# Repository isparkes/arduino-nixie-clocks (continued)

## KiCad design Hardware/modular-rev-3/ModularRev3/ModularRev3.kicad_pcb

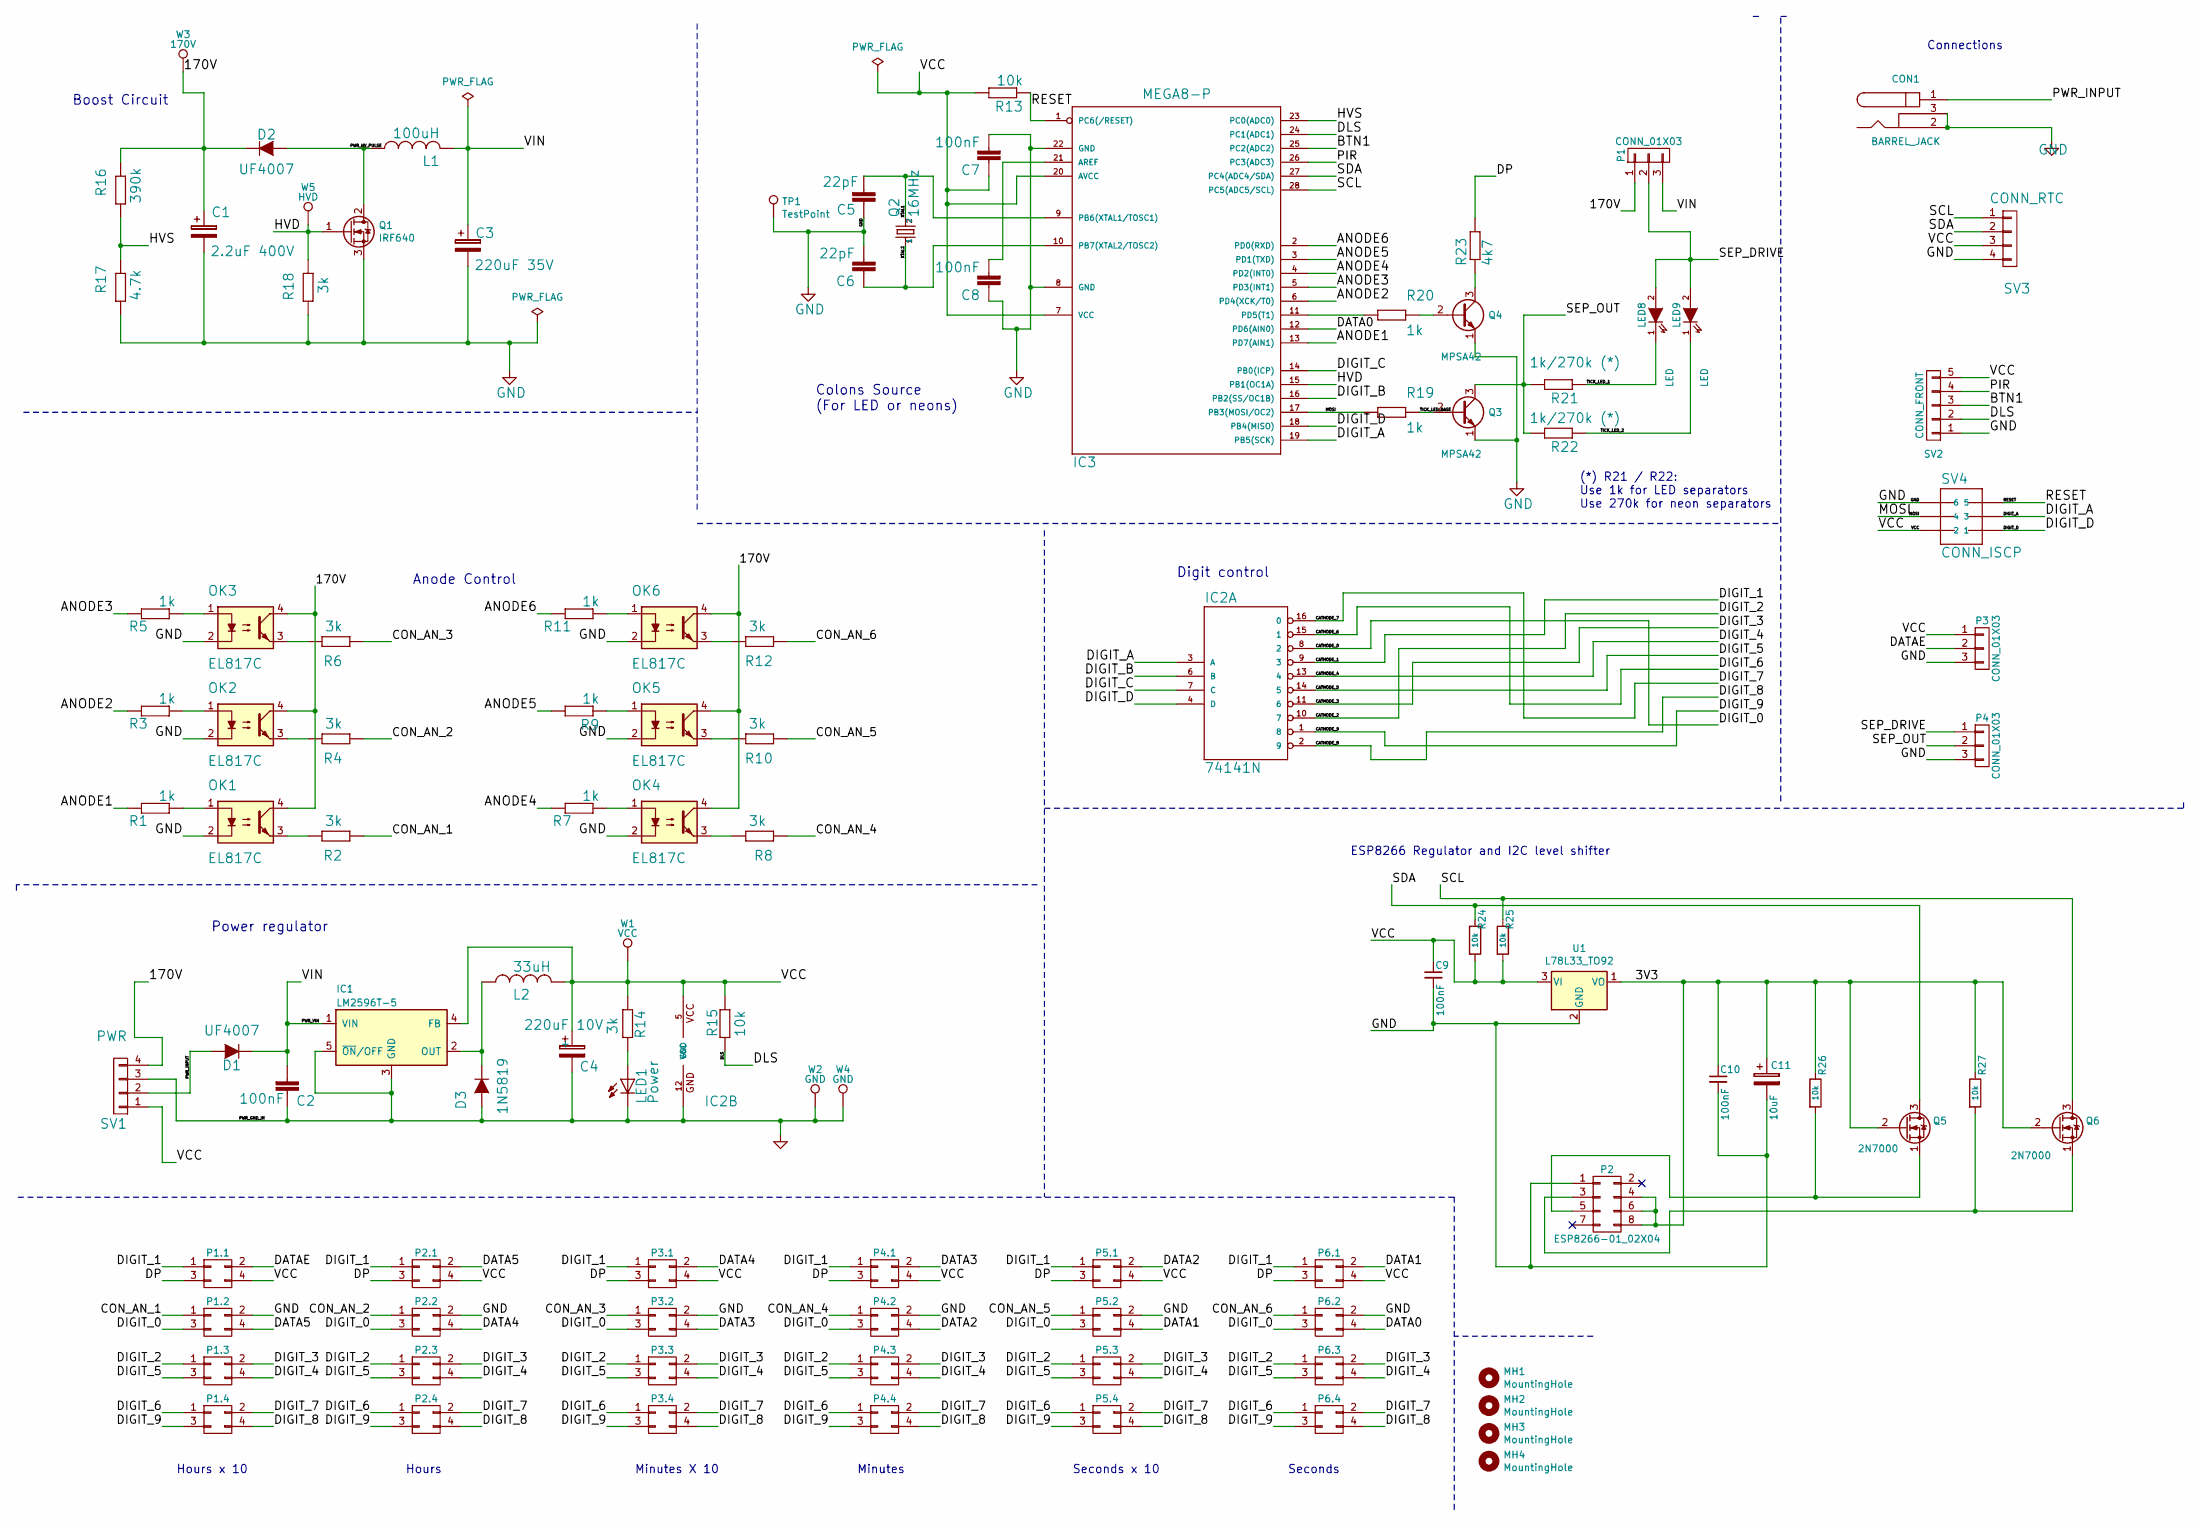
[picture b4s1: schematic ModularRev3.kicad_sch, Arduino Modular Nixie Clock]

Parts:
C1: 2.2uF 400V; C_Radial_D8_L11.5_P3.5
C2, C7, C8, C9, C10: 100nF; C025-024X044
C3: 220uF 35V; C_Radial_D8_L11.5_P3.5
C4: 220uF 10V; C_Radial_D6.3_L11.2_P2.5
C5, C6: 22pF; C025-024X044
C11: 10uF; C_Radial_D6.3_L11.2_P2.5
CON1: BARREL_JACK
D1, D2: UF4007; Diode_DO-41_SOD81_Vertical_AnodeUp
D3: 1N5819; Diode_DO-41_SOD81_Vertical_AnodeUp
IC1: LM2596T-5; TO220-5A_H
IC2: 74141N; 74141_DIL16
IC3: MEGA8-P; 328P_DIL28
L1: 100uH; Inductor-100mH
L2: 33uH; Inductor-33mH-TH-SMD
LED1: Power; LED_3MM
LED8, LED9: LED; LED-5MM-Centred
MH1, MH2, MH3, MH4: MountingHole; MountingHole_3.2mm_M3
OK1, OK2, OK3, OK4, OK5, OK6: EL817C; optocoupler-DIL04
P1: CONN_01X03; SOLDER-JUMPER_2-WAY
P1.1, P1.2, P1.3, P1.4, P2.1, P2.2, P2.3, P2.4, P3.1, P3.2, P3.3, P3.4, P4.1, P4.2, P4.3, P4.4, P5.1, P5.2, P5.3, P5.4, P6.1, P6.2, P6.3, P6.4: CONN_02X02; Header_MA02-2
P2: ESP8266-01_02X04; ESP8266_2x04
P3, P4: CONN_01X03; Header_MA03-1
Q1: IRF640; TO-220-3_H
Q2: 16MHz; Crystal_HC49-U_Vertical
Q3, Q4: MPSA42; TO-92_inline_MPSA42
Q5, Q6: 2N7000; TO-92_2N7000_inline
R1, R3, R5, R7, R9, R11, R19, R20: 1k; R-0207_2V
R2, R4, R6, R8, R10, R12, R14, R18: 3k; R-0207_2V
R13, R15, R24, R25, R26, R27: 10k; R-0207_2V
R16: 390k; R-0207_2V
R17: 4.7k; R-0207_2V
R21, R22: 1k/270k (*); R-0207_2V
R23: 4k7; R-0207_2V
SV1: PWR; Header_MA04-1
SV2: CONN_FRONT; Header_MA05-1
SV3: CONN_RTC; Header_MA04-1
SV4: CONN_ISCP; Header_MA03-2
TP1: TestPoint; TestPoint_THTPad_1.0x1.0mm_Drill0.5mm
U1: L78L33_TO92; TO-92_Inline
W1: VCC; TESTPAD_P1-13
W2, W4: GND; TESTPAD_P1-13
W3: 170V; TESTPAD_P1-13
W5: HVD; TESTPAD_P1-13

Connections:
/3V3: C10.1, C11.1, P2.4 (CH_EN), P2.6 (RST), P2.8 (VCC), Q5.2 (G), Q6.2 (G), R26.1, R27.1, U1.1 (VO)
/170V: C1.1, D2.1 (K), OK1.4, OK2.4, OK3.4, OK4.4, OK5.4, OK6.4, P1.1, R16.2, SV1.4, W3.1
/ANODE1: IC3.13 (PD7(AIN1)), R1.2
/ANODE2: IC3.6 (PD4(XCK/T0)), R3.2
/ANODE3: IC3.5 (PD3(INT1)), R5.2
/ANODE4: IC3.4 (PD2(INT0)), R7.2
/ANODE5: IC3.3 (PD1(TXD)), R9.2
/ANODE6: IC3.2 (PD0(RXD)), R11.2
/BTN1: IC3.25 (PC2(ADC2)), SV2.3
/CATHODE_0: IC2.8 (2), P1.2.3, P2.2.3, P3.2.3, P4.2.3, P5.2.3, P6.2.3
/CATHODE_1: IC2.9 (3), P1.1.1, P2.1.1, P3.1.1, P4.1.1, P5.1.1, P6.1.1
/CATHODE_2: IC2.10 (7), P1.3.1, P2.3.1, P3.3.1, P4.3.1, P5.3.1, P6.3.1
/CATHODE_3: IC2.11 (6), P1.3.2, P2.3.2, P3.3.2, P4.3.2, P5.3.2, P6.3.2
/CATHODE_4: IC2.13 (4), P1.3.4, P2.3.4, P3.3.4, P4.3.4, P5.3.4, P6.3.4
/CATHODE_5: IC2.14 (5), P1.3.3, P2.3.3, P3.3.3, P4.3.3, P5.3.3, P6.3.3
/CATHODE_6: IC2.15 (1), P1.4.1, P2.4.1, P3.4.1, P4.4.1, P5.4.1, P6.4.1
/CATHODE_7: IC2.16 (0), P1.4.2, P2.4.2, P3.4.2, P4.4.2, P5.4.2, P6.4.2
/CATHODE_8: IC2.2 (9), P1.4.4, P2.4.4, P3.4.4, P4.4.4, P5.4.4, P6.4.4
/CATHODE_9: IC2.1 (8), P1.4.3, P2.4.3, P3.4.3, P4.4.3, P5.4.3, P6.4.3
/CON_AN_1: P1.2.1, R2.1
/CON_AN_2: P2.2.1, R4.1
/CON_AN_3: P3.2.1, R6.1
/CON_AN_4: P4.2.1, R8.1
/CON_AN_5: P5.2.1, R10.1
/CON_AN_6: P6.2.1, R12.1
/DATA0: IC3.12 (PD6(AIN0)), P6.2.4
/DATA1: P5.2.4, P6.1.2
/DATA2: P4.2.4, P5.1.2
/DATA3: P3.2.4, P4.1.2
/DATA4: P2.2.4, P3.1.2
/DATA5: P1.2.4, P2.1.2
/DATAE: P1.1.2, P3.2
/DIGIT_A: IC2.3 (A), IC3.19 (PB5(SCK)), SV4.3
/DIGIT_B: IC2.6 (B), IC3.16 (PB2(SS/OC1B))
/DIGIT_C: IC2.7 (C), IC3.14 (PB0(ICP))
/DIGIT_D: IC2.4 (D), IC3.18 (PB4(MISO)), SV4.1
/DLS: IC3.24 (PC1(ADC1)), R15.1, SV2.2
/DP: P1.1.3, P2.1.3, P3.1.3, P4.1.3, P5.1.3, P6.1.3, R23.2
/HVD: IC3.15 (PB1(OC1A)), Q1.1 (G), R18.2, W5.1
/HVS: IC3.23 (PC0(ADC0)), R16.1, R17.2
/MOSI: IC3.17 (PB3(MOSI/OC2)), R19.1, SV4.4
/PIR: IC3.26 (PC3(ADC3)), SV2.4
/PWR_HV_PULSE: D2.2 (A), L1.1, Q1.2 (D)
/PWR_INPUT: CON1.1, D1.2 (A), SV1.2
/PWR_VIN: C2.2, C3.1, D1.1 (K), IC1.1 (VIN), L1.2, P1.3
/RESET: IC3.1 (PC6(/RESET)), R13.1, SV4.5
/SCL: IC3.28 (PC5(ADC5/SCL)), Q6.3 (D), R25.1, SV3.1
/SDA: IC3.27 (PC4(ADC4/SDA)), Q5.3 (D), R24.1, SV3.2
/SEP_DRIVE: LED8.2 (A), LED9.2 (A), P1.2, P4.1
/SEP_OUT: P4.2, Q3.3 (C), R21.2, R22.2
/TICK_LED_1: LED8.1 (K), R21.1
/TICK_LED_2: LED9.1 (K), R22.1
/TICK_LED_BASE: Q3.2 (B), R19.2
/VCC: C4.1, C7.1, C9.1, IC1.4 (FB), IC2.5 (VCC), IC3.7 (VCC), IC3.20 (AVCC), L2.2, P1.1.4, P2.1.4, P3.1, P3.1.4, P4.1.4, P5.1.4, P6.1.4, R13.2, R14.1, R15.2, R24.2, R25.2, SV1.1, SV2.5, SV3.3, SV4.2, U1.3 (VI), W1.1
/XTAL1: C5.2, IC3.9 (PB6(XTAL1/TOSC1)), Q2.2
/XTAL2: C6.1, IC3.10 (PB7(XTAL2/TOSC2)), Q2.1
GND: C1.2, C2.1, C3.2, C4.2, C5.1, C6.2, C7.2, C8.1, C9.2, C10.2, C11.2, CON1.2, CON1.3, D3.2 (A), IC1.3 (GND), IC1.5 (~ON/OFF), IC2.12 (GND), IC3.8 (GND), IC3.22 (GND), LED1.K (C), OK1.2, OK2.2, OK3.2, OK4.2, OK5.2, OK6.2, P1.2.2, P2.1 (GND), P2.2.2, P3.3, P3.2.2, P4.3, P4.2.2, P5.2.2, P6.2.2, Q1.3 (S), Q3.1 (E), Q4.1 (E), R17.1, R18.1, SV1.3, SV2.1, SV3.4, SV4.6, TP1.1, U1.2 (GND), W2.1, W4.1
unnamed: C8.2, IC3.21 (AREF)
unnamed: D3.1 (K), IC1.2 (OUT), L2.1
unnamed: IC3.11 (PD5(T1)), R20.1
unnamed: LED1.A, R14.2
unnamed: OK1.1, R1.1
unnamed: OK1.3, R2.2
unnamed: OK2.1, R3.1
unnamed: OK2.3, R4.2
unnamed: OK3.1, R5.1
unnamed: OK3.3, R6.2
unnamed: OK4.1, R7.1
unnamed: OK4.3, R8.2
unnamed: OK5.1, R9.1
unnamed: OK5.3, R10.2
unnamed: OK6.1, R11.1
unnamed: OK6.3, R12.2
unnamed: P2.3 (GPIO2), Q6.1 (S), R27.2
unnamed: P2.5 (GPIO0), Q5.1 (S), R26.2
unnamed: Q4.2 (B), R20.2
unnamed: Q4.3 (C), R23.1

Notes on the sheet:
Seconds x 10
Minutes
Digit control
Seconds
ESP8266 Regulator and I2C level shifter
(*) R21 / R22: Use 1k for LED separators Use 270k for neon separators
Hours
Minutes X 10
Anode Control
Colons Source (For LED or neons)
Power regulator
Connections
Boost Circuit
Hours x 10

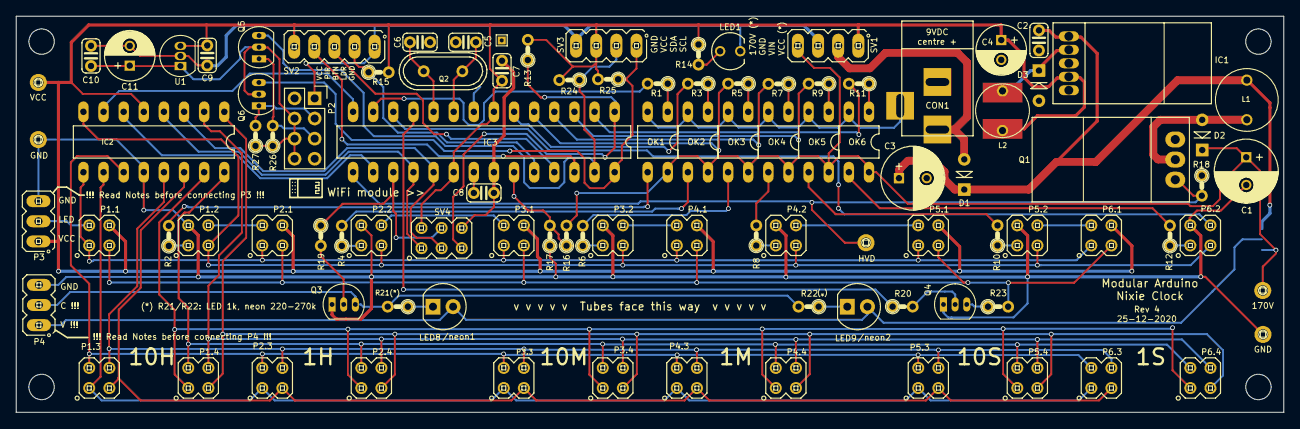
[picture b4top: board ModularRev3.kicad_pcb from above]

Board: 2 copper layers, 160.0 x 50.0 mm, 105 parts (1 on the bottom side), 77 nets.

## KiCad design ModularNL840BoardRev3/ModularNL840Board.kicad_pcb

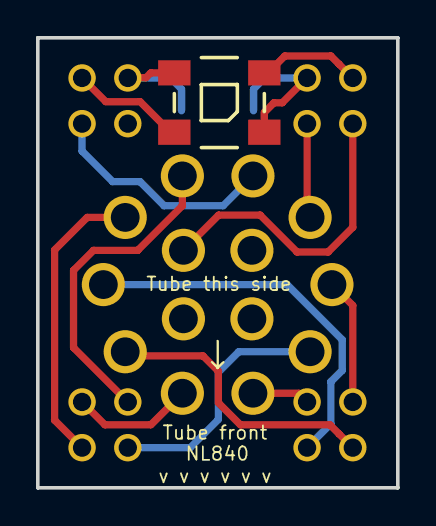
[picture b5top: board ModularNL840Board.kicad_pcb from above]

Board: 2 copper layers, 20.0 x 25.0 mm, 7 parts (1 on the bottom side), 15 nets.

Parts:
C1: C; C_1206_HandSoldering
LED1: WS2812B; WS2812B-SmallPads
N1: NL840; NL840-RTS-14-DSUB
P1.1, P1.2, P1.3, P1.4: CONN_02X02; Header_MA02-2_RearMount

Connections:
/CONN_AN_1: N1.4, P1.2.1
/DIGIT_0_1: N1.13, P1.2.3
/DIGIT_1_1: N1.5, P1.1.1
/DIGIT_2_1: N1.7, P1.3.1
/DIGIT_3_1: N1.10, P1.3.2
/DIGIT_4_1: N1.6, P1.3.4
/DIGIT_5_1: N1.2, P1.3.3
/DIGIT_6_1: N1.8, P1.4.1
/DIGIT_7_1: N1.1, P1.4.2
/DIGIT_8_1: N1.3, P1.4.4
/DIGIT_9_1: N1.9, P1.4.3
/DIN: LED1.4, P1.2.4
/DOUT: LED1.2, P1.1.2
/GND: C1.1, LED1.3, P1.2.2
/VCC: C1.2, LED1.1, P1.1.4

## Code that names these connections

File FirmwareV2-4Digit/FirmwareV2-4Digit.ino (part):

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#define EE_USE_LDR            34     // if we use the LDR or not (if we don't use the LDR, it has 100% brightness
#define EE_BLANK_MODE         35     // blank tubes, or LEDs or both
#define EE_SLOTS_MODE         36     // Show date every now and again
#define EE_PIR_TIMEOUT_LO     37     // The PIR timeout time in S, low byte
#define EE_PIR_TIMEOUT_HI     38     // The PIR timeout time in S, high byte
#define EE_PIR_PULLUP         39     // If we use the internal pullup on the PIR pin (false = use 3V3 PIR, PIR connected, true = no PIR connected or 5V PIR)
#define EE_MIN_DIM_LO         40     // The minimum dimming value, low byte
#define EE_MIN_DIM_HI         41     // The minimum dimming value, high byte

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#define MODE_ANTI_GHOST_UP              36 // 
#define MODE_ANTI_GHOST_DOWN            37 // 

// Use the PIR pin pullup resistor - Not Available over I2C
#define MODE_USE_PIR_PULLUP             38 // 1 = use Pullup
#define USE_PIR_PULLUP_DEFAULT          true

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
// SN74141/K155ID1
// These are now managed directly on PORT B, we don't use digitalWrite() for these
#define ledPin_0_a  13    // package pin 19 // PB5
#define ledPin_0_b  10    // package pin 16 // PB2
#define ledPin_0_c  8     // package pin 14 // PB0
#define ledPin_0_d  12    // package pin 18 // PB4

// anode pins
#ifdef REV3
  #define ledPin_a_1  A3  // high - Hours tens  // Package pin 26 // PC3 // Analog or digital input for PIR
#else
  #define ledPin_a_1  7   // high - Hours tens  // package pin 13 // PD7
#endif
#define ledPin_a_2  4     //      - Hours units // package pin 6  // PD4
#define ledPin_a_3  3     //      - Mins  tens  // package pin 5  // PD3
#define ledPin_a_4  2     //      - Mins  units // package pin 4  // PD2
//#define ledPin_a_5  1     //      - Secs  tens  // package pin 3  // PD1
//#define ledPin_a_6  0     // low  - Secs  units // package pin 2  // PD0

// button input
#define inputPin1   A2    // Package pin 25 // PC2 // Analog or digital input for button.

// PIR input
#ifdef REV3
  #define pirPin    7     // package pin 13 // PD7
#else
  #define pirPin    A3    // Package pin 26 // PC3 // Analog or digital input for PIR
#endif

// PWM pin used to drive the DC-DC converter
#define hvDriverPin 9     // package pin 15 // PB1

// Tick led - PWM capable
#define tickLed     11    // package pin 17 // PB3

// Decimal point - PWM capable
#define DP          5     // package pin 11 // PD5

// PWM capable output for backlight - Neo Pixel chain
#define LED_DOUT    6     // package pin 12 // PD6

#define sensorPin   A0    // Package pin 23 // PC0 // Analog input pin for HV sense: HV divided through 390k and 4k7 divider, using 5V reference
#define LDRPin      A1    // Package pin 24 // PC1 // Analog input for Light dependent resistor.

//**********************************************************************************
Transition transition(500, 1000, 3000);
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
  tccrOff = TCCR1A;

  TCCR1A |= (1 <<  COM1A1);  // enable PWM on port PD4 in non-inverted compare mode 2

  tccrOn = TCCR1A;

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  readEEPROMValues();

  // Not setting the pullup resistor allows us to use 3V3 devices (e.g. RCWL-0516)
  digitalWrite(pirPin, usePIRPullup); // set pull up resistor - if no PIR connected, default to "triggered"

  // set our PWM profile
  setPWMOnTime(pwmOn);
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// ************************************************************
// Check the PIR status. If we don't have a PIR installed, we
// don't want to respect the pin value, because it would defeat
// normal day blanking. The first time the PIR takes the pin low
// we mark that we have a PIR and we should start to respect
// the sensor.
// Returns true if PIR sensor is installed and we are blanked
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void digitOn(int digit, int value) {
  switch (digit) {
#ifdef REV3
    case 0: PORTC = PORTC | B00001000; break; // PC3 - equivalent to digitalWrite(ledPin_a_1,HIGH);
#else
    case 0: PORTD = PORTD | B10000000; break; // PD7 - equivalent to digitalWrite(ledPin_a_1,HIGH);
#endif
    case 1: PORTD = PORTD | B00010000; break; // PD4 - equivalent to digitalWrite(ledPin_a_2,HIGH);
    case 2: PORTD = PORTD | B00001000; break; // PD3 - equivalent to digitalWrite(ledPin_a_3,HIGH);
    case 3: PORTD = PORTD | B00000100; break; // PD2 - equivalent to digitalWrite(ledPin_a_4,HIGH);
    case 4: PORTD = PORTD | B00000010; break; // PD1 - equivalent to digitalWrite(ledPin_a_5,HIGH);
    case 5: PORTD = PORTD | B00000001; break; // PD0 - equivalent to digitalWrite(ledPin_a_6,HIGH);
  }
  SetSN74141Chip(value);
  TCNT1 = 0; // Thanks Phil!
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
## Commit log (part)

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2017-08-11 Add arbitrary value display
2017-08-12 Correct last digit on version display. HVG calibration LEDs.
2017-08-12 Arbitrary value mode
2017-08-13 PirTimeout in I2C, PM indicator
2017-08-13 PirTimeout, reorder options, add input disabling
2017-08-13 Correct PIR int handling
2017-08-13 Add enabling for baclight options
2017-08-13 Add ColourTime baclight option
2017-10-18 V349: Leading zero blanking in slots mode
2017-11-05 Remove pullup from PIR input
2017-11-19 Correct PIR pullup omission
2017-11-19 Colourtime dimming, thanks Derek!
2017-11-19 Correct arbitrary value format (was reversed) - more kudos to Derek
2017-11-20 Add mDNS - Derek again...
2017-12-07 Correct skip for back light options
2018-03-06 Test Mode Limit, show RTC status
2018-05-16 Allow RTC and WiFi to work together
2018-05-25 blnking seconds on calibration: simplify
2018-05-28 Deode settings for ZM1000
2018-06-13 Converge HV faster
2018-06-13 New V2 hardware layout for Classic Rev6
2018-06-15 Press on 88:88:88 to exit test mode
2018-06-15 Rename Time directory to TimeLib
2018-06-15 Add ZIP libraries for ease on installation
2018-06-15 Encapsulate button handling
2018-06-15 Make HV converge from below
2018-06-15 Temp mode version config number
2018-09-16 Add min dim setting, modularise code some more
2018-09-16 Align codebase between V1 and V2
2018-10-11 Add README
2018-10-11 Correct error on I2C setting 12/24H (thanks Andy)
2018-10-11 Bum version
2018-10-11 I mean "bump version"
2018-11-06 Add Min Dim setting, fix I2C protocol
2018-11-06 Add min dim
2018-11-15 License.md created online with Bitbucket
2018-11-26 Initial import
2019-01-01 Initial commit into Git
2019-01-08 Update to Kicad 5
2019-01-14 Transfer to Bitbucket
2019-02-10 Update settings comments
2019-02-10 50 day rollover fix
2019-02-18 Contribution from Mike Sauve - NTP code, OTA
2019-02-18 Update SDK to allow "system_restore"
2019-02-25 Converge ClassicRev6 and ModularRev301, bump version
2019-02-26 Port WiFiManager
2019-02-26 Correct AM/PM indicator reset in 24H Mode
2019-02-26 Cleanup
2019-02-26 Correct blink settings
2019-03-01 Phil's HV fix - thanks!
2019-03-03 Add support for ModRev3
2019-03-19 Transition correction - thanks Ty!
2019-03-19 Prepare for 4-Digit code
2019-03-19 Trivial: More DIGIT_COUNT instances
2019-03-19 4 Digit version
2019-03-30 Cleaned up unused/duplicated libraries
2019-04-23 TH Level shifter
2019-04-23 Add "External" schematic
2019-05-02 Correct External LEDs
2019-07-31 Correct cathode numbering: no electrical change
2019-11-13 Add ground plane around Xtal
2019-11-15 Change Q3-Q6 footprint, add can ground for xtal
2019-11-15 Add IN-8 holder board
2019-11-28 Correct IN-8 pin out
2019-12-27 Prepare for fabrication
2020-02-01 Update copyright
2020-03-06 Moved to subdirectory
2020-03-06 Add flipped version
2020-03-06 Enable B-SilkScreen
2020-03-10 Correct button menu
2020-04-16 Correct order of tubes on flip
2020-04-16 Tube other side warning
2020-04-30 Lay the TO-220s down
2020-04-30 Rename
2020-04-30 IN-8-2 version
2020-05-14 Better spacing on C1
2020-05-14 Laid down TO-220s
2020-05-15 Spacing on L1
2020-05-18 Silk screen changes for Fab
2020-05-31 Correct mirrored footprint
2020-05-31 NL-840 holder
2020-06-29 Rename PDFs
2020-07-20 THT WiFi Intf
2020-07-20 Flat Power components
2020-07-24 Increase spacing between 170V and GND
2020-07-24 Remove CAM files
2020-07-31 Minor SS changes
2020-09-19 Better NTP and GUI
2020-09-21 Weird, didn't show up on 1.8.13
2020-09-21 Correct TZS on restart
2020-09-22 AP SSID
2020-09-22 Update Header
2020-10-06 Add "slots mode" to the menu
2020-10-09 Better formatting of strings
2020-10-09 Correct summary display
2020-10-25 On the top IN-8-2
2020-10-25 Rename IN14 on the top
2020-10-25 Pour under inductor
2020-10-28 Z570 version
2020-10-30 Small changes for Fab.
2020-11-15 Minor Silk Screen corrections
2020-11-20 Correct MPSA42 in schematic
2020-11-25 Update DP resistor to 4k7
2020-12-06 Add dp handling V2
2020-12-25 Minor corrections to BoM
2020-12-26 Rev4
2020-12-28 Correct DRC problem on DOUT
2020-12-31 Update anode numbering
2021-01-01 Fills
2021-01-26 Create fp file
2021-01-29 Update fpcache
2021-02-15 Correct compiler error on Windows
2021-02-19 Protocol v2p64
2021-02-19 v2p64 blank dim option
2021-02-19 Re-enable value display
2021-02-19 Correct alarm time input
2021-02-20 Add status for p64
2021-03-28 External tube wiring
2021-04-03 Improve WiFi reconnection (once per hour and brutally once per day)
2021-04-03 Fix MinDim on v2p64
2021-04-06 Moved from "NixieFirmwareV2"
2021-04-06 Move Repo
2021-04-07 Clean up
2021-04-28 Allow ESP01S (but without LED)
2021-05-27 Don't hang when an invalid NTP pool is set
2021-06-16 Update to new board settings
2021-06-27 Update ESP01 handling
2021-09-28 spacing
2021-10-01 Break out server set up functions
2021-10-16 Refresh, add mounting holes to schematic, more dimensions
2021-10-16 Refresh
2022-05-15 New TH Production
2022-05-15 Minor adjustments new fabrication
2022-05-15 Classic R5 new production
2022-10-20 Update KiCad 5
2023-07-12 Kicad6
2023-10-27 Update to Kicad6
2023-11-23 Change LED footprints
2024-01-07 Complete IN-8 board
2024-01-31 Update ignores
2024-03-17 Update to THT Wifi
2024-03-18 Update footprints
2024-03-30 Update KiCAD6
2024-12-21 Ignore backups
2025-01-05 Update to Kicad 6
2025-02-28 New edition
2025-02-28 Change to TH WiFi interface
2025-04-29 Updates for new fab
